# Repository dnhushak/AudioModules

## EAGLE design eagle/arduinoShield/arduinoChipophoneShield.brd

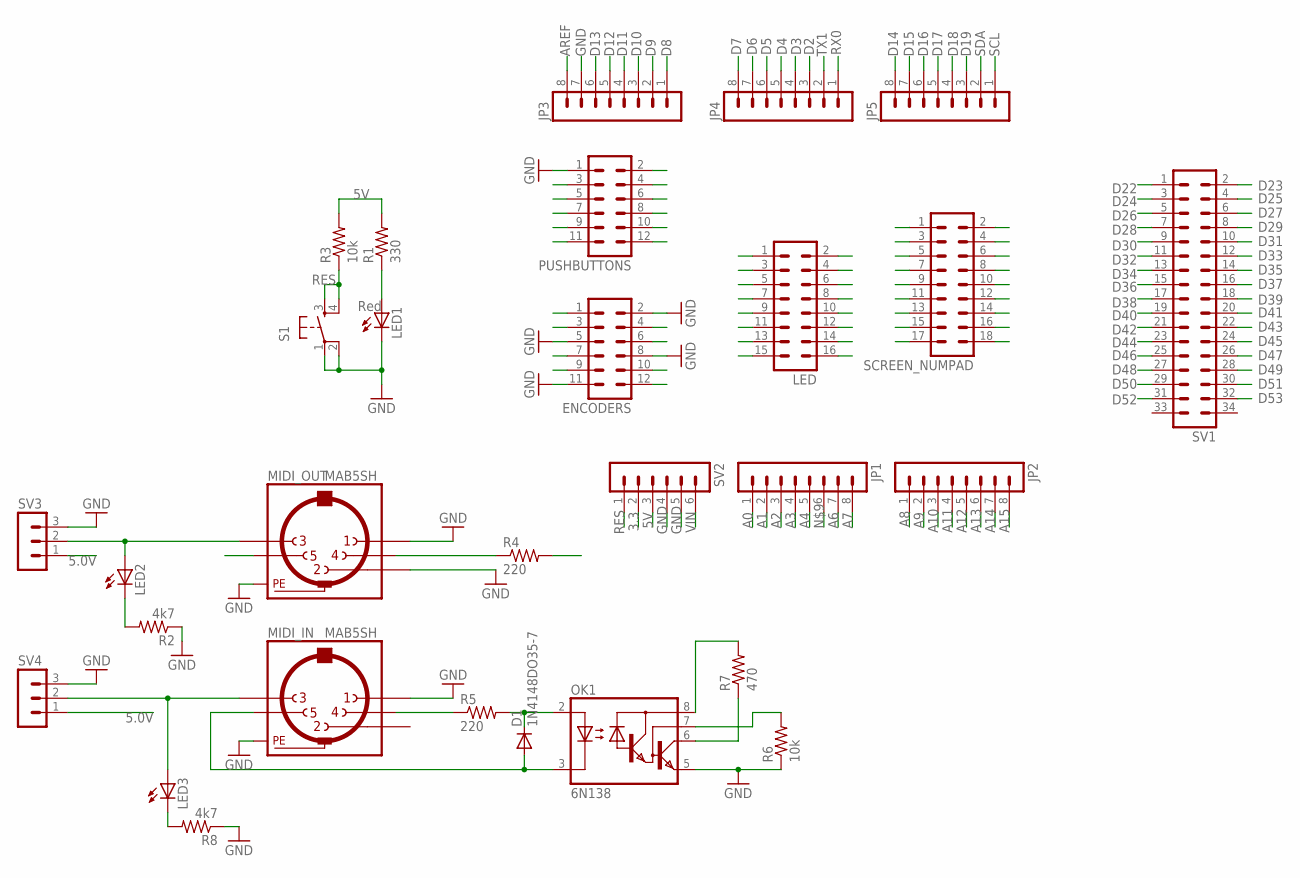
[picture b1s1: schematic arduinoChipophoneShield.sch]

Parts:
D1: 1N4148DO35-7; DO35-7
ENCODERS: MA06-2
JP1, JP2, JP3, JP4, JP5: MA08-1
LED: MA08-2
LED1: Red; LED5MM
LED2, LED3: LEDLSU260; LSU260
MIDI_IN: MAB5SH
MIDI_OUT: MAB5SH
OK1: 6N138; DIL08
PUSHBUTTONS: MA06-2
R1: 330; AXIAL-0.3
R2, R8: 4k7; 0204/7
R3: 10k; AXIAL-0.3
R4, R5: 220; 0204/7
R6: 10k; 0204/7
R7: 470; 0204/7
S1: TAC_SWITCHPTH; TACTILE-PTH
SCREEN_NUMPAD: MA09-2
SV1: MA17-2
SV2: MA06-1
SV3, SV4: MA03-1

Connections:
3.3: SV2.2
5V: LED.1, OK1.8 (VCC), R1.P$2 (2), R3.P$2 (2), R4.2, R7.2, SCREEN_NUMPAD.1, SCREEN_NUMPAD.9, SV2.3, SV3.1, SV4.1
A0: JP1.1, SCREEN_NUMPAD.11
A1: JP1.2, SCREEN_NUMPAD.12
A2: JP1.3, SCREEN_NUMPAD.13
A3: JP1.4, SCREEN_NUMPAD.14
A4: JP1.5, SCREEN_NUMPAD.15
A6: JP1.7, SCREEN_NUMPAD.17
A7: JP1.8, SCREEN_NUMPAD.18
A8: JP2.1
A9: JP2.2
A10: JP2.3
A11: JP2.4
A12: JP2.5
A13: JP2.6
A14: JP2.7
A15: JP2.8
AREF: JP3.8
D2: JP4.3, LED.2
D3: JP4.4, LED.3
D4: JP4.5, LED.4
D5: JP4.6, LED.5
D6: JP4.7, LED.6
D7: JP4.8, LED.7
D8: JP3.1, LED.8
D9: JP3.2, LED.9
D10: JP3.3, LED.10
D11: JP3.4, LED.11
D12: JP3.5, LED.12
D13: JP3.6, LED.13
D14: JP5.8
D15: JP5.7
D16: JP5.6
D17: JP5.5
D18: JP5.4, MIDI_OUT.5
D19: JP5.3, OK1.6 (VO), R7.1
D22: PUSHBUTTONS.2, SV1.1
D23: PUSHBUTTONS.3, SV1.2
D24: PUSHBUTTONS.4, SV1.3
D25: PUSHBUTTONS.5, SV1.4
D26: PUSHBUTTONS.6, SV1.5
D27: PUSHBUTTONS.7, SV1.6
D28: PUSHBUTTONS.8, SV1.7
D29: PUSHBUTTONS.9, SV1.8
D30: PUSHBUTTONS.10, SV1.9
D31: PUSHBUTTONS.11, SV1.10
D32: PUSHBUTTONS.12, SV1.11
D33: ENCODERS.1, SV1.12
D34: ENCODERS.3, SV1.13
D35: ENCODERS.4, SV1.14
D36: ENCODERS.6, SV1.15
D37: ENCODERS.7, SV1.16
D38: ENCODERS.9, SV1.17
D39: ENCODERS.10, SV1.18
D40: ENCODERS.12, SV1.19
D41: SV1.20
D42: SV1.21
D43: SV1.22
D44: LED.14, SV1.23
D45: LED.15, SV1.24
D46: LED.16, SV1.25
D47: SV1.26
D48: SCREEN_NUMPAD.6, SV1.27
D49: SCREEN_NUMPAD.7, SV1.28
D50: SCREEN_NUMPAD.2, SV1.29
D51: SCREEN_NUMPAD.4, SV1.30
D52: SCREEN_NUMPAD.3, SV1.31
D53: SCREEN_NUMPAD.5, SV1.32
GND: ENCODERS.2, ENCODERS.5, ENCODERS.8, ENCODERS.11, JP3.7, LED1.K (C), MIDI_IN.1, MIDI_IN.PE, MIDI_IN.PE@ (PE), MIDI_OUT.1, MIDI_OUT.2, MIDI_OUT.PE, MIDI_OUT.PE@ (PE), OK1.5 (GND), PUSHBUTTONS.1, R2.1, R6.1, R8.1, S1.1, S1.2, SCREEN_NUMPAD.10, SV2.4, SV2.5, SV3.3, SV4.3
unnamed: LED3.A, MIDI_IN.3, SV4.2
unnamed: LED2.A, MIDI_OUT.3, SV3.2
unnamed: MIDI_OUT.4, R4.1
unnamed: LED2.K (C), R2.2
unnamed: D1.C, OK1.2 (A), R5.2
unnamed: MIDI_IN.4, R5.1
unnamed: D1.A, MIDI_IN.5, OK1.3 (C)
unnamed: OK1.7 (VB), R6.2
unnamed: JP1.6, SCREEN_NUMPAD.16
unnamed: LED3.K (C), R8.2
unnamed: LED1.A, R1.P$1 (1)
RES: R3.P$1 (1), S1.3, S1.4, SCREEN_NUMPAD.8, SV2.1
RX0: JP4.1
SCL: JP5.1
SDA: JP5.2
TX1: JP4.2
VIN: SV2.6

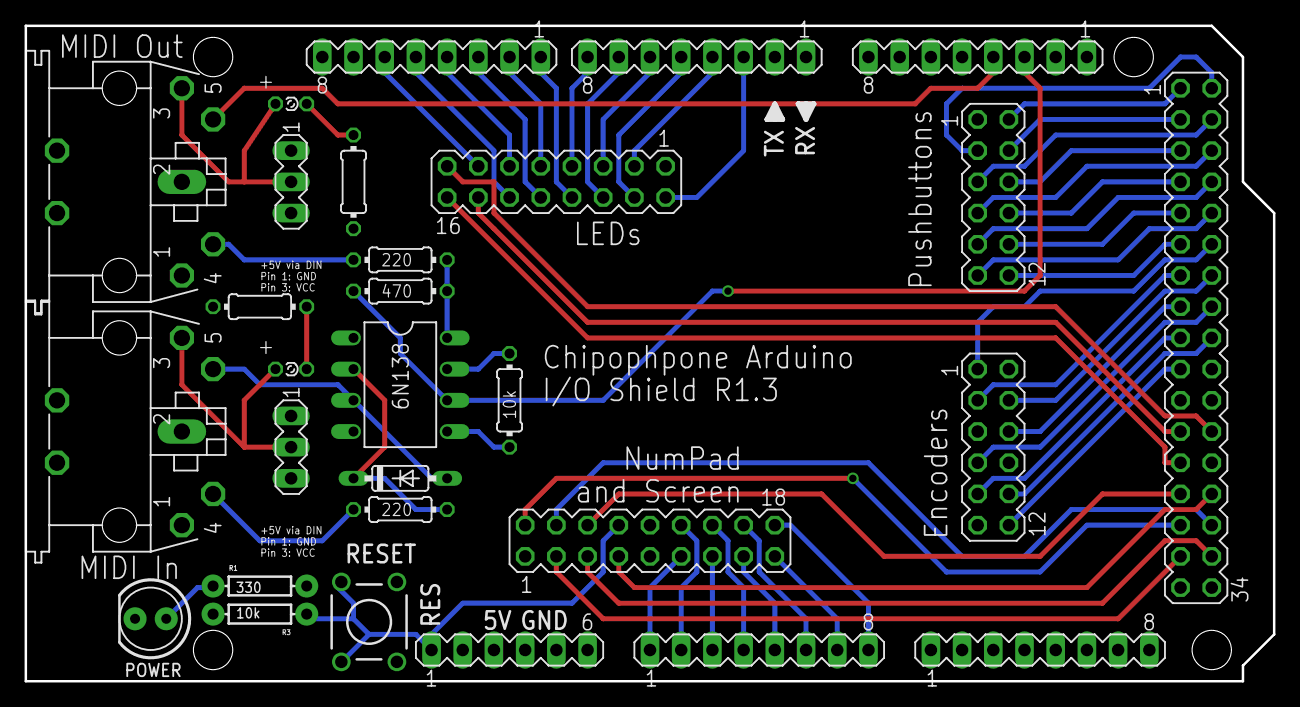
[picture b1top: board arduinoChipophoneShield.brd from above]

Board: 2 copper layers, 101.6 x 53.3 mm, 29 parts (0 on the bottom side), 63 nets.

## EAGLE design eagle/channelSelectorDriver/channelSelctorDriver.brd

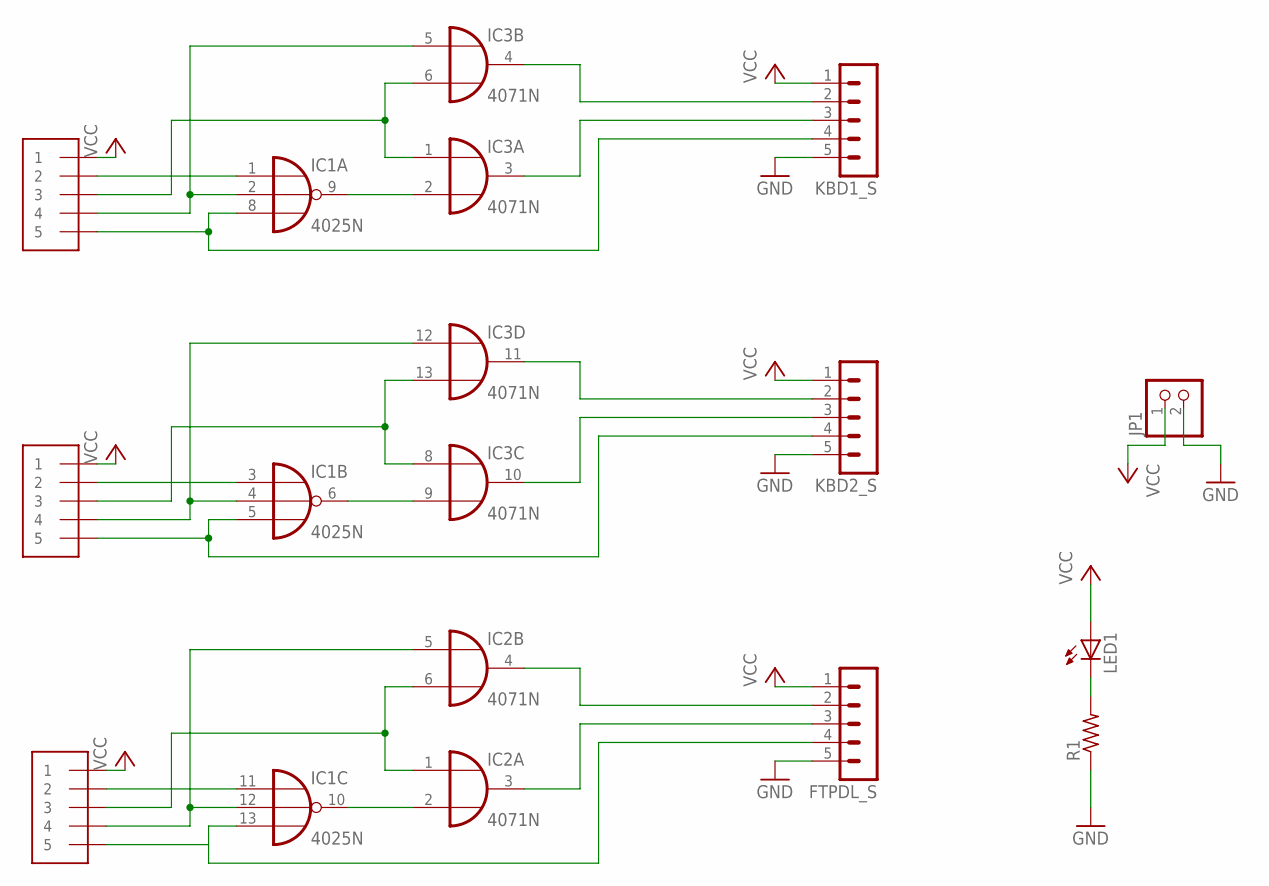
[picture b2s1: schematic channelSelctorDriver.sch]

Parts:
FTPDL_S: MA05-1
IC1: 4025N; DIL14
IC2, IC3: 4071N; DIL14
JP1: PINHD-1X2; 1X02
KBD1_C, KBD2_C, KBD3_C: 1X5; 1X05-3.5MM
KBD1_S, KBD2_S: MA05-1
LED1: LEDLSU260; LSU260
R1: R-US_0204/7; 0204/7

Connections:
GND: FTPDL_S.5, IC1.7 (VSS), IC2.7 (VSS), IC3.7 (VSS), JP1.2, KBD1_S.5, KBD2_S.5, R1.1
unnamed: IC1.9 (O), IC3.2 (I1)
unnamed: IC1.6 (O), IC3.9 (I1)
unnamed: IC1.10 (O), IC2.2 (I1)
unnamed: IC1.5 (I2), KBD2_C.5, KBD2_S.4
unnamed: IC1.2 (I1), IC3.5 (I0), KBD1_C.4
unnamed: IC1.12 (I1), IC2.5 (I0), KBD3_C.4
unnamed: IC3.1 (I0), IC3.6 (I1), KBD1_C.3
unnamed: IC3.4 (O), KBD1_S.2
unnamed: IC3.3 (O), KBD1_S.3
unnamed: IC1.1 (I0), KBD1_C.2
unnamed: IC1.11 (I0), KBD3_C.2
unnamed: LED1.K (C), R1.2
unnamed: IC3.11 (O), KBD2_S.2
unnamed: IC3.10 (O), KBD2_S.3
unnamed: IC3.8 (I0), IC3.13 (I1), KBD2_C.3
unnamed: IC1.4 (I1), IC3.12 (I0), KBD2_C.4
unnamed: FTPDL_S.4, IC1.13 (I2), KBD3_C.5
unnamed: IC2.1 (I0), IC2.6 (I1), KBD3_C.3
unnamed: FTPDL_S.2, IC2.4 (O)
unnamed: FTPDL_S.3, IC2.3 (O)
unnamed: IC1.8 (I2), KBD1_C.5, KBD1_S.4
unnamed: IC1.3 (I0), KBD2_C.2
VCC: FTPDL_S.1, IC1.14 (VDD), IC2.14 (VDD), IC3.14 (VDD), JP1.1, KBD1_C.1, KBD1_S.1, KBD2_C.1, KBD2_S.1, KBD3_C.1, LED1.A

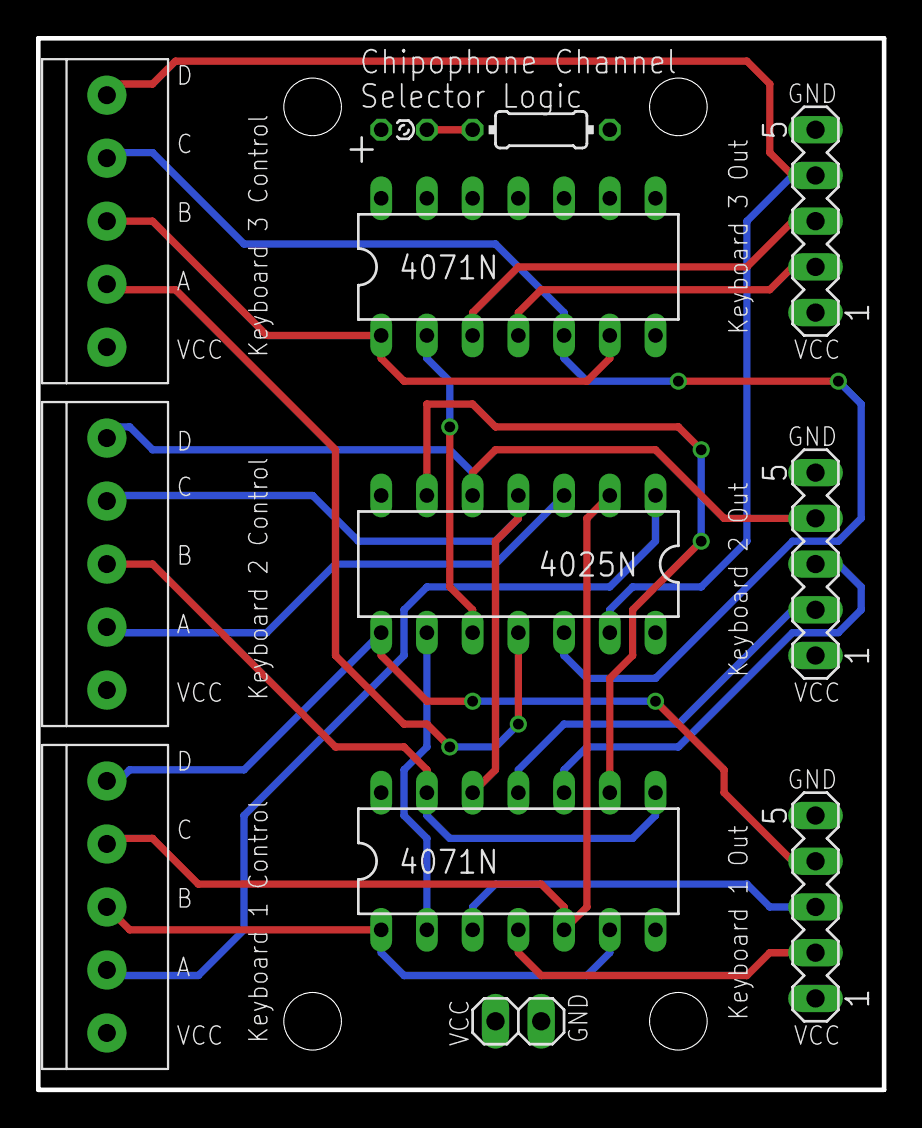
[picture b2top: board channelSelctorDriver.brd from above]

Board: 2 copper layers, 47.0 x 58.4 mm, 12 parts (0 on the bottom side), 24 nets.

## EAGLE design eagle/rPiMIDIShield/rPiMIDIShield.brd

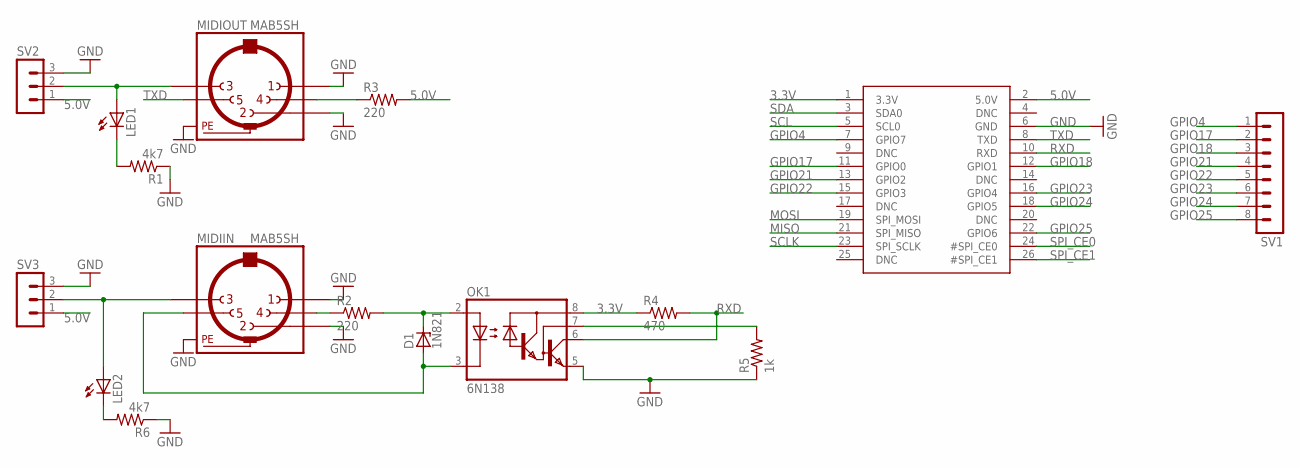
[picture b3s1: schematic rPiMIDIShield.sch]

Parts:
D1: 1N821; DO35Z10
GPIO: RASPBERRYPI_BB; RASBERRYPI_SHIELD
LED1, LED2: LEDLSU260; LSU260
MIDIIN: MAB5SH
MIDIOUT: MAB5SH
OK1: 6N138; DIL08
R1, R6: 4k7; 0204/7
R2, R3: 220; 0204/7
R4: 470; 0204/7
R5: 1k; 0204/7
SV1: MA08-1
SV2, SV3: MA03-1

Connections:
3.3V: GPIO.1 (3.3V), OK1.8 (VCC), R4.1
5.0V: GPIO.2 (5.0V), R3.2, SV2.1, SV3.1
GND: GPIO.6 (GND), MIDIIN.1, MIDIIN.2, MIDIIN.PE, MIDIIN.PE@ (PE), MIDIOUT.1, MIDIOUT.2, MIDIOUT.PE, MIDIOUT.PE@ (PE), OK1.5 (GND), R1.1, R5.1, R6.1, SV2.3, SV3.3
GPIO4: GPIO.7 (GPIO7), SV1.1
GPIO17: GPIO.11 (GPIO0), SV1.2
GPIO18: GPIO.12 (GPIO1), SV1.3
GPIO21: GPIO.13 (GPIO2), SV1.4
GPIO22: GPIO.15 (GPIO3), SV1.5
GPIO23: GPIO.16 (GPIO4), SV1.6
GPIO24: GPIO.18 (GPIO5), SV1.7
GPIO25: GPIO.22 (GPIO6), SV1.8
MISO: GPIO.21 (SPI_MISO)
MOSI: GPIO.19 (SPI_MOSI)
unnamed: LED2.A, MIDIIN.3, SV3.2
unnamed: LED1.A, MIDIOUT.3, SV2.2
unnamed: MIDIOUT.4, R3.1
unnamed: MIDIIN.4, R2.1
unnamed: LED1.K (C), R1.2
unnamed: OK1.7 (VB), R5.2
unnamed: D1.A, MIDIIN.5, OK1.3 (C)
unnamed: D1.C, OK1.2 (A), R2.2
unnamed: LED2.K (C), R6.2
RXD: GPIO.10 (RXD), OK1.6 (VO), R4.2
SCL: GPIO.5 (SCL0)
SCLK: GPIO.23 (SPI_SCLK)
SDA: GPIO.3 (SDA0)
SPI_CE0: GPIO.24 (#SPI_CE0)
SPI_CE1: GPIO.26 (#SPI_CE1)
TXD: GPIO.8 (TXD), MIDIOUT.5

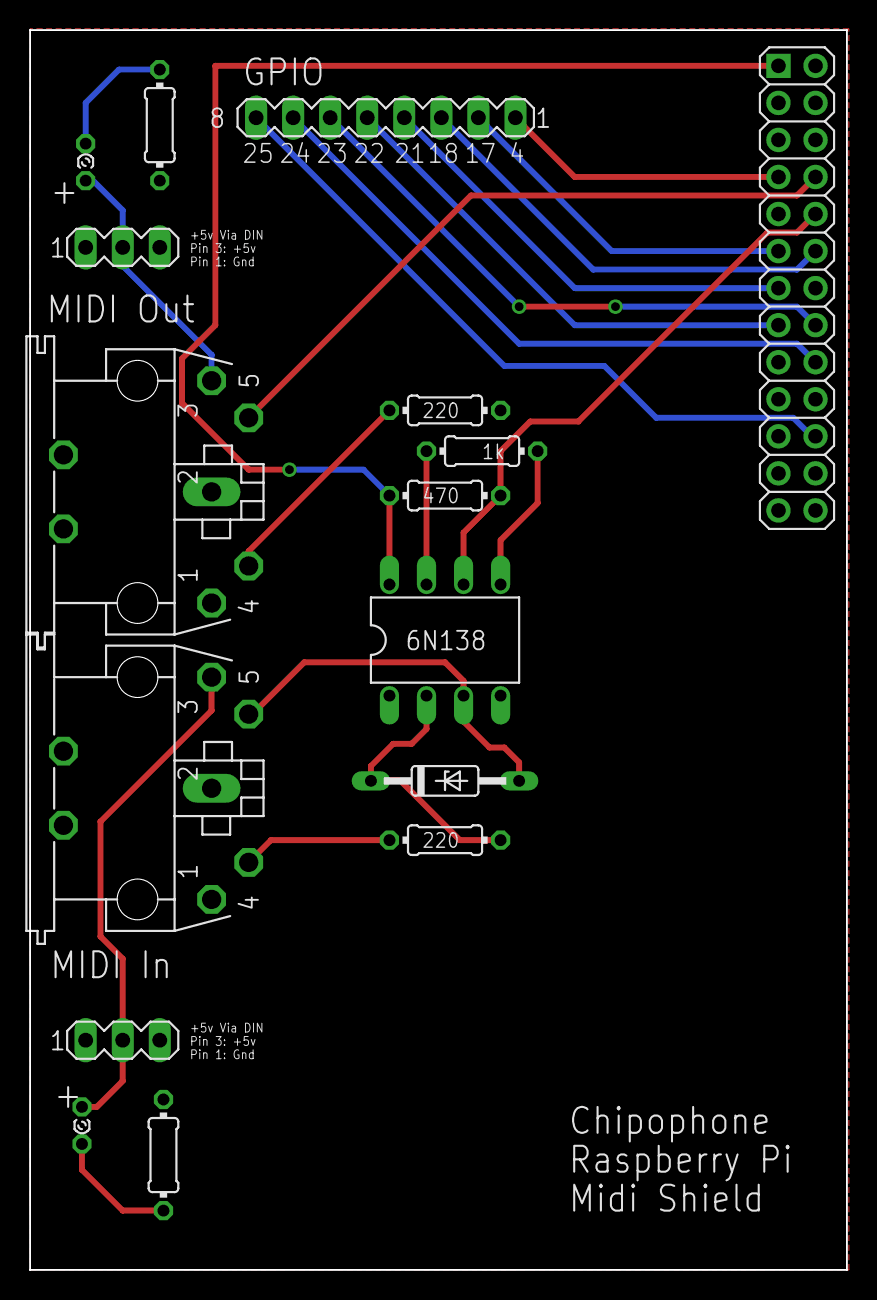
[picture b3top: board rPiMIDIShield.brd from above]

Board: 2 copper layers, 56.0 x 85.0 mm, 16 parts (0 on the bottom side), 22 nets.

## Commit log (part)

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2014-01-22 Added MIDI I/O, took out status light
2014-01-22 removed .pro file
2014-01-23 Added drill holes to channel selector board
2014-01-25 Added an easter egg
2014-02-08 Utilities
2014-02-13 Created and completed MIDI Shield for Raspberry Pi
2014-02-13 Modified the labels so they don't show up on silkscreen. Also moved all components within eagle's 'Approved Board Size'
2014-02-19 Added switches for 5v supply via MIDI
2014-02-19 Added ground/power plane as well as 5V DIN forwarding switches on Arduino Board
2014-02-21 ignore
2014-02-25 Updated makefile
2014-02-25 Fix'd Makefile
2014-02-26 Removed extraneous printing during the callback, actually make things much smoother
2014-02-26 Updated gitignore
2014-02-26 Updated makefile to install config file too. Added the voices config text file
2014-03-03 Updated Module to dynamically allocate/deallocate polyvoices using the std::vector built in functions
2014-03-04 Edited polyVoices to extend the IAudio interface, moving to add a mixer to each module
2014-03-04 Fixed the allocation/reallocation issues
2014-03-04 Mixer now working fully. MixerTest also updated to new mixer architecture
2014-03-04 Removed the darren folder, it was time. Also updated the Synthesizer to accept optargs
2014-03-05 Updating polyvoice to new style of buffer forwarding
2014-03-06 More updates to the envelope class
2014-03-07 Completed Envelope, Wavetable and oscillator classes
2014-03-07 Added a ramp component. Working on PolyVoice/Module/Voice integration
2014-03-07 Added a gain module
2014-03-07 Split out PM and PA functionality into their own handlers
2014-03-07 Alll...mooost.... theerrrree.........
2014-03-07 More MIDIProcessor work. Updated AudioEffect to have a maximum number of devices in its device list
2014-03-07 Updated maximum behavior for AudioEffects
2014-03-07 Created MIDI Channel Filter, and actually added the files this time
2014-03-09 Made MIDI Printer device. Also updated audio effect to not automatically include setMaxNumDevices
2014-03-09 Removed MIDIController class - moved functionality to PMHandler class
2014-03-09 Almost there. Testing out some of the revamping by just printing MIDI
2014-03-09 More cleaning
2014-03-10 Fixed several kinks in the Port MIDI handler
2014-03-10 REALLY figured out virtual destructors now
2014-03-10 More pretty colors
2014-03-11 Lots of bug fixes. Testing Envelope responses currently
2014-03-11 Found issue in the polyvoice to be vibrato causing problems
2014-03-11 Actually gets rid of unused polyVoices now with a delete
2014-03-11 Fixed vibrato
2014-03-11 Fixed triangle wave. Added MIDI Channel filtering
2014-03-12 Using iterators for polyVoice deallocation
2014-03-12 Iterator referencing issues
2014-03-12 Completed dynamic voice reallocation - just made it triggered via MIDI instead of a while loop
2014-03-12 Fixed a std::free declaration
2014-03-12 Moooore compiler error fixes
2014-03-13 Attempting O3 compiler optimization
2014-03-13 Implemented a brickwall limiter - perhaps that's what's causing ALSA crunch?
2014-03-13 Free pointers to buffers on destruction
2014-03-13 Switched the cleanup back to the while loop, now with the proper memory management
2014-03-17 Attempting to see if it's the while loop causing problems
2014-03-20 fixed segfaulting via access of non existent list item
2014-03-23 Even more makefile cleaning.
2014-03-24 Another default
2014-03-27 Editing mutex locks
2014-03-27 Moved the realtime enable down
2014-03-27 Removed crazy stuff
2014-03-27 Changed around the lock to include the remove within said lock
2014-03-27 Added a threaded cleanup, so cleanup only works while there are active voices
2014-03-28 Fixed data races, deadlocks, hung notes by further correcting lock placements
2014-03-28 Renamed namespace
2014-03-28 Virtual base class Device
2014-03-28 Removed extraneous functions
2014-03-30 Experimenting with realloc... having abort trap errors...
2014-04-01 Fixed alter after free problems
2014-04-01 removed weffc+, it gives outdated errors
2014-04-01 Cleaned a few things up
2014-04-02 Lots of the UI work
2014-04-02 Encoders and Pushbutton labels were swapped
2014-04-02 Got encoder class to work using fancy XOR methodology
2014-04-02 Removed tests, they're out of date and no longer indicative of the codebase
2014-04-03 Created an enum for system message types. Now using song select system message to select song, program change for voices. (makes sense, right?)
2014-04-03 Minor tweak
2014-04-03 Added blink and toggle to RGBLED
2014-04-03 Finishing up the behavior for the songbox control
2014-04-03 Completed songbox control
2014-04-03 Moved to top folder, no need for subfolder
2014-04-03 Changed argument name
2014-04-03 Fixed state checking, also fixed Pause LED not lighting on pause state
2014-04-03 Implemented "hasChanged()" on encoders
2014-04-03 Module Control complete. Needs testing
2014-04-03 Completed UI Code (without testing)
2014-04-04 Renamed .ino to make Arduino happy
2014-04-04 Removed extras
2014-04-04 Finally builds on Arduino. Now to test....
2014-04-04 Updated message printer to include system commands
2014-04-04 Testing Songbox Control
2014-04-04 Updated gitignore to ignore Chipophone Executable
2014-04-04 Fixed faulty logic on whether or not to send second data byte
2014-04-04 Fixed the off() never turning things off.
2014-04-04 Updated to R1.2, which fixes the missing Pin on the screen header. Also has CS connected now too
2014-04-04 Halved the size of the board. Much smaller, much cheaper.
2014-04-04 Started on screen controller. Now for some ideas on what to put on the screen.....
2014-04-09 Big Commit. Changed to the ConnectableDevice class, making the list management much easier.
2014-04-09 Changed back to a memcpy function. Kept old version in comments just in case.
2014-04-09 ConnectableDevice Template Class
2014-04-09 Minor improvements to the mixer
2014-04-09 MIDI Utils files
2014-04-09 Switched to easy-to-change sample type.
2014-04-09 Updating for archlinux
2014-04-09 Changed the affect() method from a sending type to a receiving type. ReadMIDI() now forwards to all connected devices using the private forward() class.
2014-04-19 Switched the switches around so ON points to the LED, makes more sense that way.
2014-05-02 Forgot about tempo encoder. Need to add that in yet.
2014-05-04 Added Tempo Encoder
2014-05-04 Still have some issues with song select being sent. Not sure if it's arduino or downtream
2014-08-06 Switching to standardized library
2014-08-06 Removed pragma onces, added ifndef and defines to handle duplicate declarations
2014-08-07 Made wavetable a device
2014-08-07 Todo comment
2014-08-07 Created a sample-accurate VCA
2014-08-07 Added an additional set, non-sample based gain stage
2014-08-07 Returned the list accessors to public functions
2014-08-18 Changed "limiter" to "clipper," as that's much more accurate of its behavior
2014-08-18 Segregated namespaces for main, module, and polyvoice.
2014-08-19 Added a setTableSize method that allows the wavetable to be dynamically resized.
2014-08-19 Fixed an error where referencing bufferSize instead of tableSize
2014-08-19 Getting rid of (temporarily) the parameter function endeavor
2014-08-19 Applied the use of read() again to save for loop overhead
2014-09-01 Chaning around the advance/read functionality
2014-09-03 Created a VCO object, allowing the frequency of an oscillator to be adjusted by a connected device.
2014-09-04 Use the copyToBuffer method instead of another memcpy statement. Cleaner.
2014-09-18 Fixed numSamples -> bufferSize. Also moved envloc++ outside of the loop, as the locator will always increase by buffer size every time
2014-09-18 Sh*t compiles now
2014-09-18 Attempting to fix preproccessor infinite loops with the AudioEngine class
2014-11-03 Included ConnectableDevice
2014-11-06 Rethinking the audio engine item. Coming up with something different...
2014-11-06 Comment formatting
2014-11-06 Using ```endOfBuffer``` from the ```AudioDevice``` to reset all audio devices at the end of buffers
2014-11-06 Delay time seems to not respond correctly. Added a TODO
2014-11-06 Fixed delay - was looking into future instead of past. Oooooooops. Divide by zero and all that.
2014-11-07 Still not working, need to figure out a good algorithm for the bitcrusher
2014-11-07 Fixed a cast away from float causing the multiplier to default to 0
2014-11-15 Got code from the chipophone UI to start on the Arduino MIDI devices
2014-11-15 Working on the MIDI Read function
2014-11-15 Change all hpp to h files
2014-11-15 Cleanup
2014-11-15 Fixed an unsigned issue and added includes
2015-01-02 Added a thoughts text file for scratch thinking
2015-01-19 Made connectableDevice only able to be a child of Device (finally)
2015-01-19 That did not do what I thought it was supposed to do
2015-01-19 Created and got a lot of headway on a generic polyphonic handler
2015-01-19 Renamed addDevice and removeDevice to connect and disconnect device
2015-01-21 Making clone covariant across classes
2015-01-22 Updated Parameter to be able to have any number of params
2015-01-22 Created the Alterable mixin class, to allow for generalized parameterization of public functions of many devices
2015-01-22 Updated any mention of Connectable
2015-01-22 Testing out Alterable on clipper
2015-01-22 Not sure what I updated here.
2015-01-22 Implemented Alterable's alter() function
2015-01-22 Implemented alter() for several more devices
2015-01-29 Wrote a Cdoc description for alterable
2015-01-29 Added using namespace std statement to clean up a little bit
2015-02-04 Updated files to be able to write an AudioUnit from the device class tree
2015-02-04 Got a start on reworking a bufferless AudioProcessor style class heirarchy
2015-12-14 Got the damn thing to build.. Calling it a night
2015-12-14 Removed ```cloneAndConnect``` and ```cloneWithConnectable```
2015-12-14 Took out parameter type for now
2015-12-14 Got rid of filter files - unnecessary extra at this point
2015-12-14 FINALLY SOLVED THE TREE CLONE ISSUE.
    Since every device has to implement clone, if it's a connectable device
    it will need a check for clone arguments, otherwise the argument is
    unused. This allows all devices to be cloned, but also trees to be
    cloned with "nodes" being defined by objects that do not have a check
    for clone arguments. bleh.
2015-12-14 Added the check for recursive cloning.
2015-12-14 Cleaned a few lines
2015-12-15 A different approach to the connectable thing
2017-02-02 Getting closer to a valid clone() methodology
2017-02-02 Added mushroom sound just to make sure the freakin thing works. [it do]
2017-02-02 Updating priorities
2017-02-02 PolyphonicHandler builds now! Proper typing and casting (using ->second from the iterator)
2017-02-02 Completed tree erasure of connectable devices.
2017-02-03 Updated with float value
2017-02-03 Renamed "affect" to "process"
2017-02-03 Changed the param to double instead of float
2017-02-03 Changed the iteration method so it's not C++11
    Removin' warnings
2017-02-03 Allowed for an option to delete the tree, but not the object itself
2017-02-03 Created MIDI Processor. Still thinking through how exactly it'll work
2017-02-03 Fix'd data races for the cleanup phase.
2017-02-03 Testing a bunch of polyphonic functionality
2017-02-03 Formatting changes
2017-02-03 Bit of debugging, not much changed
2017-02-03 Updated numParameters value
2017-02-03 Changed something
2017-02-03 Added comments for recursive alter()
2017-02-03 Added a deactivateAllVoices method
